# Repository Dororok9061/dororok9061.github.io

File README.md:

<p align="center">
  
</p>

<p align="center">

</p>

# Hyeongrok Ryu Engineering Portfolio

The multilingual, multi-page Jekyll source for
[dororok9061.github.io](https://dororok9061.github.io/). It connects public
evidence across radar signal processing, Vision AI, sensor fusion, embedded
systems, FPGA RTL/DV, biomedical AI, systems engineering, publications,
coursework, and engineering study notes.

## ViScan · CES 2027 · Korean patent application

- **CES 2027 Innovation Awards:** application submitted
- **CES 2027:** planned ViScan booth operation and live product demonstration
- **Korean patent application:** **10-2026-0154726**, filed **August 18, 2026**
- **Filing title:** *Ultrasound-Based Smart Mirror Body Composition Analysis System* / **초음파 기반 스마트미러 체성분 분석 시스템**
- **Role:** co-inventor
- **Applicants:** Dankook University Cheonan Campus Industry-Academic Cooperation Foundation and Hansono Co., Ltd.
- [Open the disclosure-safe ViScan case study](https://dororok9061.github.io/projects/viscan/)

> This is a patent application, not a granted or registered patent. No CES award result is claimed before the official announcement.

## Research Case Study framework

The existing Jekyll 4 + Simplex visual theme is preserved. The visible
[Start Here research hub](https://dororok9061.github.io/blog/start-here/) adopts
the paper-page reading model used by the iNdra research template:

```text
Abstract and resource buttons
→ Research map
→ Methodology
→ Results
→ Image gallery
→ Publications
→ Coursework and study paths
→ Code, Notion, and citation resources
```

The same structure is layered across projects, publications, coursework,
technical blog posts, STM32/PADS/mmWave study units, and external-learning
notes. Material-style SVG icons are used in the website navigation, resource
buttons, methodology flow, and GitHub banners.

### Representative case studies

| Domain | Website case study | Repository case study |
|---|---|---|
| Radar · Vision AI · Sensor Fusion · Digital Health | [ViScan Smart Mirror](https://dororok9061.github.io/projects/viscan/) | Disclosure-safe public page; private engineering repository |
| FMCW Radar · ECG/SCG sensing | [FMCW Radar Cardiac Timing](https://dororok9061.github.io/projects/fmcw-radar/) | [RESEARCH_CASE_STUDY.md](https://github.com/Dororok9061/fmcw-radar-aoac-cardiac-analysis/blob/main/RESEARCH_CASE_STUDY.md) |
| PPG · HRV · Biomedical AI | [PPG–HRV Cognitive Load](https://dororok9061.github.io/projects/ppg-hrv/) | [RESEARCH_CASE_STUDY.md](https://github.com/Dororok9061/PPG-HRV-Cognitive-Load-CNN/blob/main/RESEARCH_CASE_STUDY.md) |
| FPGA RTL · Digital Verification | [FPGA Delay Logic](https://dororok9061.github.io/projects/fpga-delay-logic/) | [RESEARCH_CASE_STUDY.md](https://github.com/Dororok9061/fpga-delay-logic-design-verification/blob/main/RESEARCH_CASE_STUDY.md) |
| Vision · Embedded Systems | [Drowsiness Monitor](https://dororok9061.github.io/projects/drowsiness-monitor/) | [RESEARCH_CASE_STUDY.md](https://github.com/Dororok9061/Sleep-monitoring-and-prevention-device/blob/main/RESEARCH_CASE_STUDY.md) |
| Electrical Engineering Coursework | [Coursework hub](https://dororok9061.github.io/coursework/) | [RESEARCH_CASE_STUDY.md](https://github.com/Dororok9061/electrical-engineering-coursework-portfolio/blob/main/RESEARCH_CASE_STUDY.md) |

The homepage exposes a dark research gateway before the original personal hero.
The navigation also contains a direct **Research Hub** entry, so the new
structure is visible without scrolling to the bottom of the site.

## Figure strategy and PaperBanana

Existing experiment photographs, source-derived plots, waveforms, circuit
screens, and report figures remain the preferred assets. When a publishable
architecture or methodology figure is missing, the page first renders a
source-based SVG/HTML concept flow. The current visible example is:

- [Portfolio methodology figure](src/assets/images/research/start-here-methodology.svg)

PaperBanana is prepared as a second-stage academic-figure workflow for
high-resolution replacements:

- [PaperBanana workflow](docs/PAPERBANANA_FIGURE_WORKFLOW.md)
- [Figure backlog and prompts](docs/paperbanana_figures.yml)

A PaperBanana output is not published as an experiment figure until every
label, arrow, component, and numeric value has been checked against the linked
source. Generated figures must not invent measurements, hardware, model scores,
PPA, clinical claims, certifications, or CES award results.

The PCB inspection publication portal is mirrored as a full static GitHub Pages
workbench, not only as a compact gallery summary:

- [PCB Research Publication Workbench](https://dororok9061.github.io/projects/pcb-visual-inspection/research-portal/?fresh=20260808-public-mirror-v1#methodology)
- [PCB project page](https://dororok9061.github.io/projects/pcb-visual-inspection/)
- [PCB mirror blog note](https://dororok9061.github.io/blog/2026/08/08/pcb-research-portal-public-mirror/)

## Theme and architecture

- Jekyll `4.4.1`
- actual Gem Theme: `jekyll-theme-simplex 0.9.8.15` (MIT)
- Korean and English routes with independent project, publication, coursework,
  defense, role, lab, blog, category, about, and security pages
- static HTML/CSS output with small first-party Vanilla JavaScript files for
  accessible navigation, image lightbox, search, section tracking, and BibTeX copy
- no database, authentication, API, form backend, analytics, ads, chat,
  Service Worker, or runtime framework
- GitHub Actions build and Pages deployment with every Action pinned to a full
  commit SHA

`src/` is the Jekyll source and `_site/` is the generated, ignored output. The
previous hand-authored site remains in `site/` only as a recovery snapshot; the
deployment workflow does not publish it.

## Build and validate

```bash
bundle install
JEKYLL_ENV=production bundle exec jekyll build --source src --destination _site --trace
python3 scripts/check_site.py _site
pwsh scripts/security/verify-site-security.ps1 -SiteRoot .
pwsh scripts/security/verify-site-security.ps1 -SiteRoot _site -BuiltSite
```

Windows PowerShell can invoke the scanner with:

```powershell
powershell.exe -NoProfile -ExecutionPolicy Bypass `
  -File scripts/security/verify-site-security.ps1 -SiteRoot _site -BuiltSite
```

After deployment:

```powershell
powershell.exe -NoProfile -ExecutionPolicy Bypass `
  -File scripts/security/verify-site-security.ps1 `
  -SiteRoot _site -BuiltSite `
  -PublicUrl "https://dororok9061.github.io/" -Online
```

## Documentation

- [Project inventory](docs/inventory/PROJECT_INVENTORY.md)
- [Notion inventory](docs/inventory/NOTION_INVENTORY.md)
- [Theme audit](docs/design/THEME_AUDIT.md)
- [Theme decision](docs/design/THEME_DECISION.md)
- [Third-party notices](docs/design/THIRD_PARTY_NOTICES.md)
- [Profile asset status](docs/PROFILE_ASSET_STATUS.md)
- [Threat model](docs/security/THREAT_MODEL.md)
- [Security architecture](docs/security/SECURITY_ARCHITECTURE.md)
- [Data classification](docs/security/DATA_CLASSIFICATION.md)
- [Deployment verification report](docs/security/VERIFICATION_REPORT_2026-07-31.md)

## Public evidence rule

Source files, rerun simulations, measured hardware results, generated
illustrations, and proposed future work are kept distinct. Missing evidence is
not converted into a pass or a measured result.

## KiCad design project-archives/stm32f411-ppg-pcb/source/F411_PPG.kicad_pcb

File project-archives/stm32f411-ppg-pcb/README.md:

# STM32F411 PPG Analog Front-End PCB

## Scope

This KiCad design integrates:

- STM32F411RETx (LQFP64);
- two SFH7070 optical sensors;
- three dual OPA2333 zero-drift amplifiers;
- 5 V input and SPX3819 3.3 V regulation;
- 8 MHz and 32.768 kHz clocks;
- SWD and UART interfaces.

The two analog channels terminate at MCU ADC inputs A0 and A1. The board is a
two-layer design with bottom-side ground copper.

## Design summary

- Approximate outline: 80.6 mm x 52.2 mm
- Modules: 69
- Nets: 83
- Tracks: 602
- Plated holes: 56

## Included files

- `source/Analog.sch` and `source/STM.sch`: hierarchical circuit sheets
- `source/F411_PPG-cache.lib` and `source/F411_PPG-rescue.lib`: legacy symbol libraries required by the schematic
- `source/F411_PPG.kicad_pcb`: PCB layout
- `source/F411_PPG.kicad_pro` and legacy project files
- `source/gerber 411_PPG/`: copper, mask, paste, silkscreen, outline, job, and drill outputs

Backups, temporary netlists, caches, and plot-map PostScript files were omitted.

## Limits

The archive reaches schematic, routing, and fabrication-output stages. It does
not include bench-measured waveforms, SNR, filter cutoff, biosignal accuracy,
EMC/thermal results, or automotive qualification.

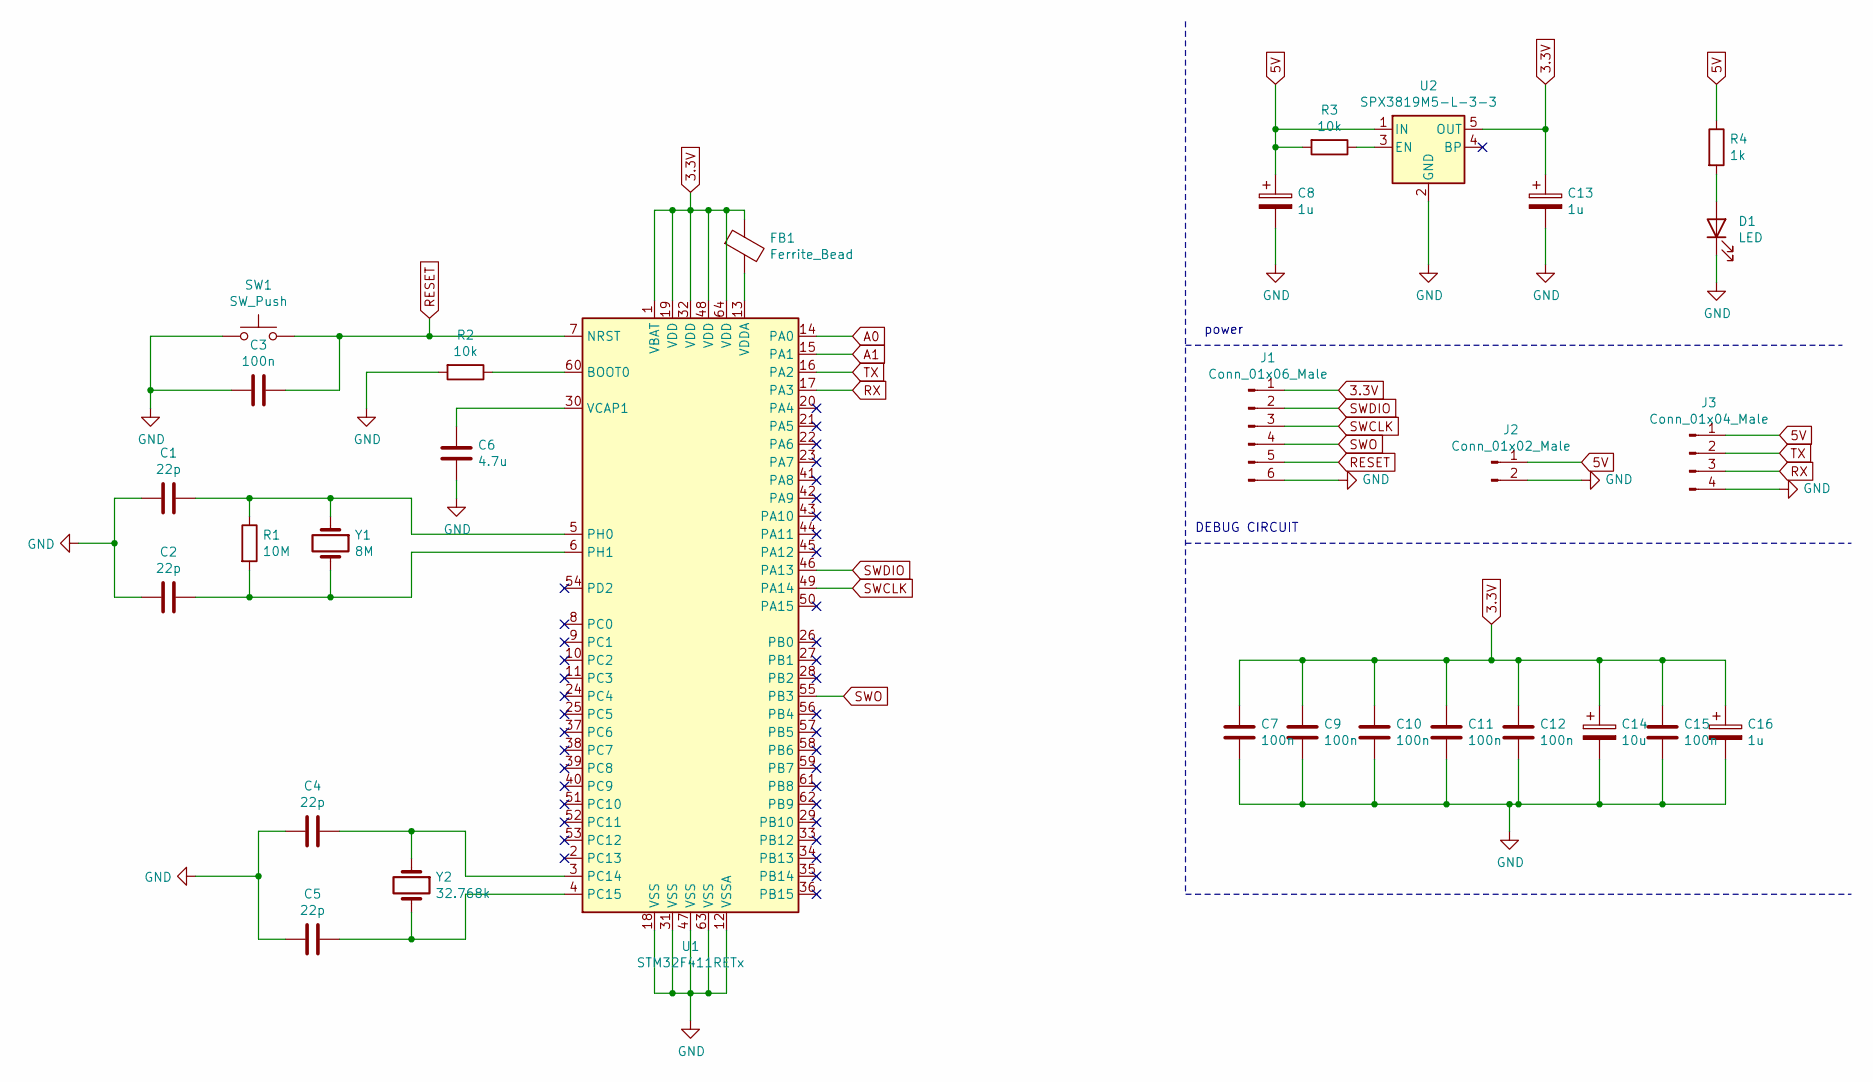
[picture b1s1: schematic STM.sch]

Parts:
C1, C2, C4, C5: 22p; C_0603_1608Metric_Pad1.08x0.95mm_HandSolder
C3, C7, C9, C10, C11, C12, C15: 100n; C_0603_1608Metric_Pad1.08x0.95mm_HandSolder
C6: 4.7u; C_0805_2012Metric_Pad1.18x1.45mm_HandSolder
C8, C13, C16: 1u; CP_EIA-3216-18_Kemet-A_Pad1.58x1.35mm_HandSolder
C14: 10u; CP_EIA-3216-18_Kemet-A_Pad1.58x1.35mm_HandSolder
D1: LED; LED_0805_2012Metric_Pad1.15x1.40mm_HandSolder
FB1: Ferrite_Bead; R_0603_1608Metric_Pad0.98x0.95mm_HandSolder
J1: Conn_01x06_Male; PinHeader_1x06_P2.54mm_Vertical
J2: Conn_01x02_Male; PinHeader_1x02_P2.54mm_Vertical
J3: Conn_01x04_Male; PinHeader_1x04_P2.54mm_Vertical
R1: 10M; R_0603_1608Metric_Pad0.98x0.95mm_HandSolder
R2, R3: 10k; R_0603_1608Metric_Pad0.98x0.95mm_HandSolder
R4: 1k; R_0603_1608Metric_Pad0.98x0.95mm_HandSolder
SW1: SW_Push; SW_SPST_CK_RS282G05A3
U1: STM32F411RETx; LQFP-64_10x10mm_P0.5mm
U2: SPX3819M5-L-3-3; SOT-23-5
Y1: 8M; Crystal_SMD_0603-2Pin_6.0x3.5mm
Y2: 32.768k; Crystal_SMD_0603-2Pin_6.0x3.5mm

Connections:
3.3V: C7.2, C9.2, C10.2, C11.2, C12.2, C13.1, C14.1, C15.2, C16.1, FB1.1, J1.1, U1.1 (VBAT), U1.19 (VDD), U1.32 (VDD), U1.48 (VDD), U1.64 (VDD), U2.5 (OUT); also elsewhere on the board
5V: C8.1, J2.1, J3.1, R3.2, R4.1, U2.1 (IN)
A0: U1.14 (PA0); also elsewhere on the board
A1: U1.15 (PA1); also elsewhere on the board
GND: C1.2, C2.2, C3.2, C4.2, C5.2, C6.1, C7.1, C8.2, C9.1, C10.1, C11.1, C12.1, C13.2, C14.2, C15.1, C16.2, D1.1 (K), J1.6, J2.2, J3.4, R2.2, SW1.1, U1.12 (VSSA), U1.18 (VSS), U1.31 (VSS), U1.47 (VSS), U1.63 (VSS), U2.2 (GND); also elsewhere on the board
unnamed: C1.1, R1.1, U1.5 (PH0), Y1.1
unnamed: C2.1, R1.2, U1.6 (PH1), Y1.2
unnamed: C4.1, U1.3 (PC14), Y2.1
unnamed: C5.1, U1.4 (PC15), Y2.2
unnamed: C6.2, U1.30 (VCAP1)
unnamed: D1.2 (A), R4.2
unnamed: FB1.2, U1.13 (VDDA)
unnamed: R2.1, U1.60 (BOOT0)
unnamed: R3.1, U2.3 (EN)
RESET: C3.1, J1.5, SW1.2, U1.7 (NRST)
RX: J3.3, U1.17 (PA3)
SWCLK: J1.3, U1.49 (PA14)
SWDIO: J1.2, U1.46 (PA13)
SWO: J1.4, U1.55 (PB3)
TX: J3.2, U1.16 (PA2)

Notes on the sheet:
power
DEBUG CIRCUIT

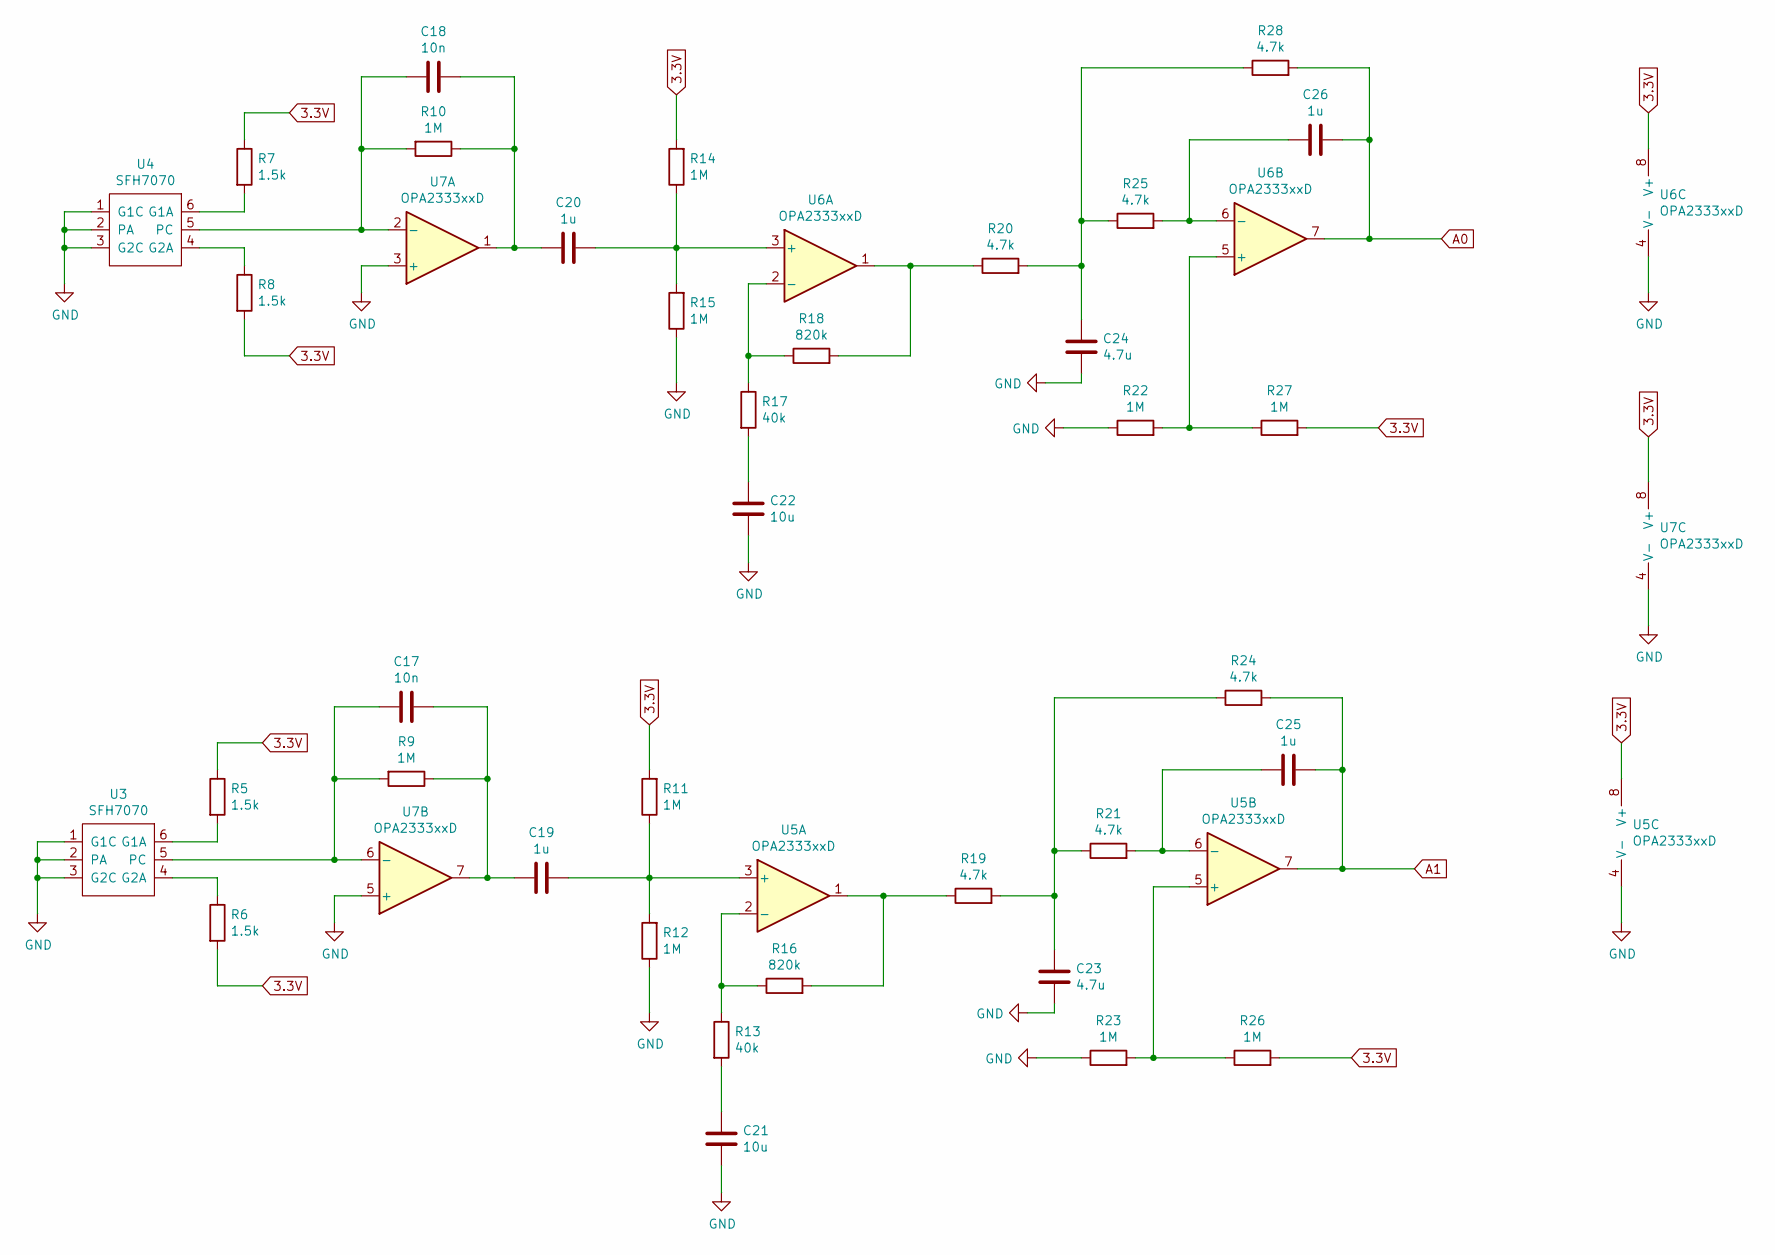
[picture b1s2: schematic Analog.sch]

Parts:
C17, C18: 10n; C_0603_1608Metric_Pad1.08x0.95mm_HandSolder
C19, C20, C25, C26: 1u; C_0603_1608Metric_Pad1.08x0.95mm_HandSolder
C21, C22: 10u; C_0603_1608Metric_Pad1.08x0.95mm_HandSolder
C23, C24: 4.7u; C_0805_2012Metric_Pad1.18x1.45mm_HandSolder
R5, R6, R7, R8: 1.5k; R_0603_1608Metric_Pad0.98x0.95mm_HandSolder
R9, R10, R11, R12, R14, R15, R22, R23, R26, R27: 1M; R_0603_1608Metric_Pad0.98x0.95mm_HandSolder
R13, R17: 40k; R_0603_1608Metric_Pad0.98x0.95mm_HandSolder
R16, R18: 820k; R_0603_1608Metric_Pad0.98x0.95mm_HandSolder
R19, R20, R21, R24, R25, R28: 4.7k; R_0603_1608Metric_Pad0.98x0.95mm_HandSolder
U3, U4: SFH7070
U5, U6, U7: OPA2333xxD; SOIC-8_3.9x4.9mm_P1.27mm

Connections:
3.3V: R5.1, R6.2, R7.1, R8.2, R11.2, R14.2, R26.2, R27.2, U5.8 (V+), U6.8 (V+), U7.8 (V+); also elsewhere on the board
A0: C26.2, R28.2, U6.7; also elsewhere on the board
A1: C25.2, R24.2, U5.7; also elsewhere on the board
GND: C21.1, C22.1, C23.2, C24.2, R12.1, R15.1, R22.1, R23.1, U3.1 (G1C), U3.2 (PA), U3.3 (G2C), U4.1 (G1C), U4.2 (PA), U4.3 (G2C), U5.4 (V-), U6.4 (V-), U7.3 (+), U7.4 (V-), U7.5 (+); also elsewhere on the board
unnamed: C17.1, C19.2, R9.1, U7.7
unnamed: C17.2, R9.2, U3.5 (PC), U7.6 (-)
unnamed: C18.1, C20.2, R10.1, U7.1
unnamed: C18.2, R10.2, U4.5 (PC), U7.2 (-)
unnamed: C19.1, R11.1, R12.2, U5.3 (+)
unnamed: C20.1, R14.1, R15.2, U6.3 (+)
unnamed: C21.2, R13.2
unnamed: C22.2, R17.2
unnamed: C23.1, R19.2, R21.1, R24.1
unnamed: C24.1, R20.2, R25.1, R28.1
unnamed: C25.1, R21.2, U5.6 (-)
unnamed: C26.1, R25.2, U6.6 (-)
unnamed: R5.2, U3.6 (G1A)
unnamed: R6.1, U3.4 (G2A)
unnamed: R7.2, U4.6 (G1A)
unnamed: R8.1, U4.4 (G2A)
unnamed: R13.1, R16.1, U5.2 (-)
unnamed: R16.2, R19.1, U5.1
unnamed: R17.1, R18.1, U6.2 (-)
unnamed: R18.2, R20.1, U6.1
unnamed: R22.2, R27.1, U6.5 (+)
unnamed: R23.2, R26.1, U5.5 (+)

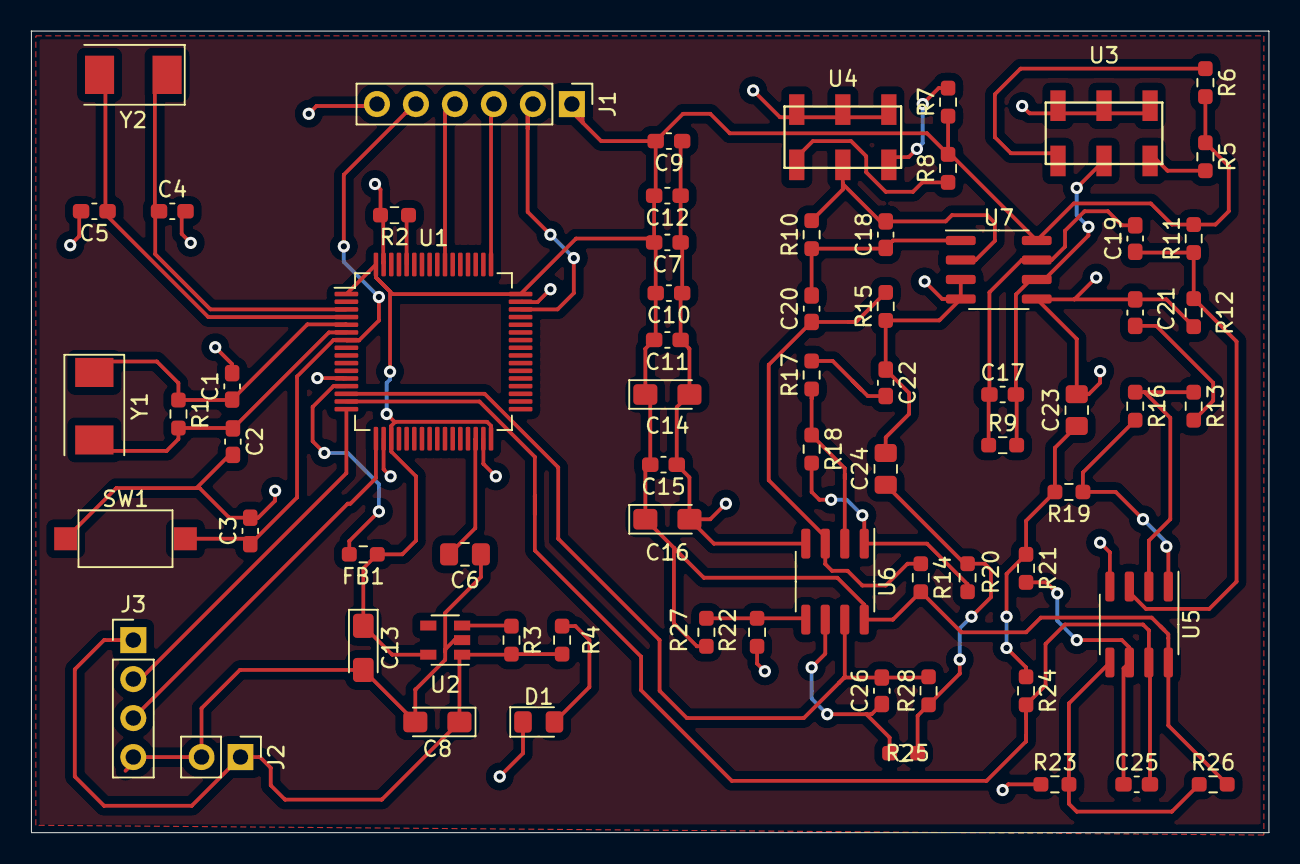
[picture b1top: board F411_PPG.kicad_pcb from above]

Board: 2 copper layers, 80.7 x 52.2 mm, 69 parts (0 on the bottom side), 42 nets.
